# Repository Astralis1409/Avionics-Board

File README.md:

# 🛰️ CubeSat Avionics / OBC / C&DH Board

A high-reliability, low-power **On-Board Computer (OBC)** and **Command & Data Handling (C&DH)** system for VikramSat, designed for modularity, simplicity, and mission-critical operations.

> 🚀 Built for student, research, and commercial CubeSat missions.

---

## 📦 Overview

This repository contains hardware and software for the CubeSat **Avionics/OBC/C&DH subsystem**, including:

- ⚙️ Real-time telemetry and telecommand handling
- 🧠 Robust on-board computing (fault-tolerant firmware)
- 📡 Interfaces for RF, EPS, ADCS, and payload communication
- 🔒 Watchdog and fault detection mechanisms

Designed with space heritage and mission resilience in mind.

---

## 🧩 Subsystems & Features

### ✅ Key Features
- RPi RP2350 based OBC
- Redundant data buses: I2C, CAN, UART, SPI, USB
- FRAM or MRAM for persistent data storageP
- Telemetry packet generation & error checking (CRC/Checksums)
- Built-in watchdog and brownout recovery
- RTOS support (FreeRTOS)

### 📡 Interfaces
- EPS (power control, reset logic)
- [VikramSat RF subsystem](https://github.com/keyaan-07/vikramsat-rf-subsystem) (telecommand & telemetry)
- ADCS (attitude determination feedback/control)
- Payload connector (Camera)

---

## 🧠 Architecture

---

## 🛠️ Hardware

- PCB: 2 layer (FR-4)
- Components:
  - MCU: [RPi RP2350](https://raspberrypi.com/products/rp2350)
  - Memory: FRAM/MRAM (TBD)
  - Power: LDOs, and TVS/ESD protection
- Connectors: USB / Bus header / Debugger

📁 See `/hardware/` for schematics and layout (EasyEDA).

> **NOTE** : The project is under development. Hence all the components and the design may change as per the requirement.

---

## 🧪 Software

- Written in MicroPython
- RTOS support (FreeRTOS)
- Fault-tolerant state machine
- Packet parsing, command dispatcher, watchdog

📁 See `/firmware/` for source code and build instructions.

> **NOTE** : The project is under development and the software is still in its initial stages. The code may change as per the requirement.

---

## 🤝 Contributing

We welcome contributors — whether you're improving the firmware, suggesting hardware improvements, or testing!

```
# Fork, clone, and create your branch
git checkout -b feature/your-feature
```

---
## 📜 License

MIT — open-source, with mission-critical use in mind.

---

## 🧑‍🚀 Credits

Developed by Jaydev parmar

Thanks to [Hack Club](https://github.com/hackclub)

With contributions from open-source spaceflight communities 🛸

> *"Space is not the final frontier — it's just the beginning."*

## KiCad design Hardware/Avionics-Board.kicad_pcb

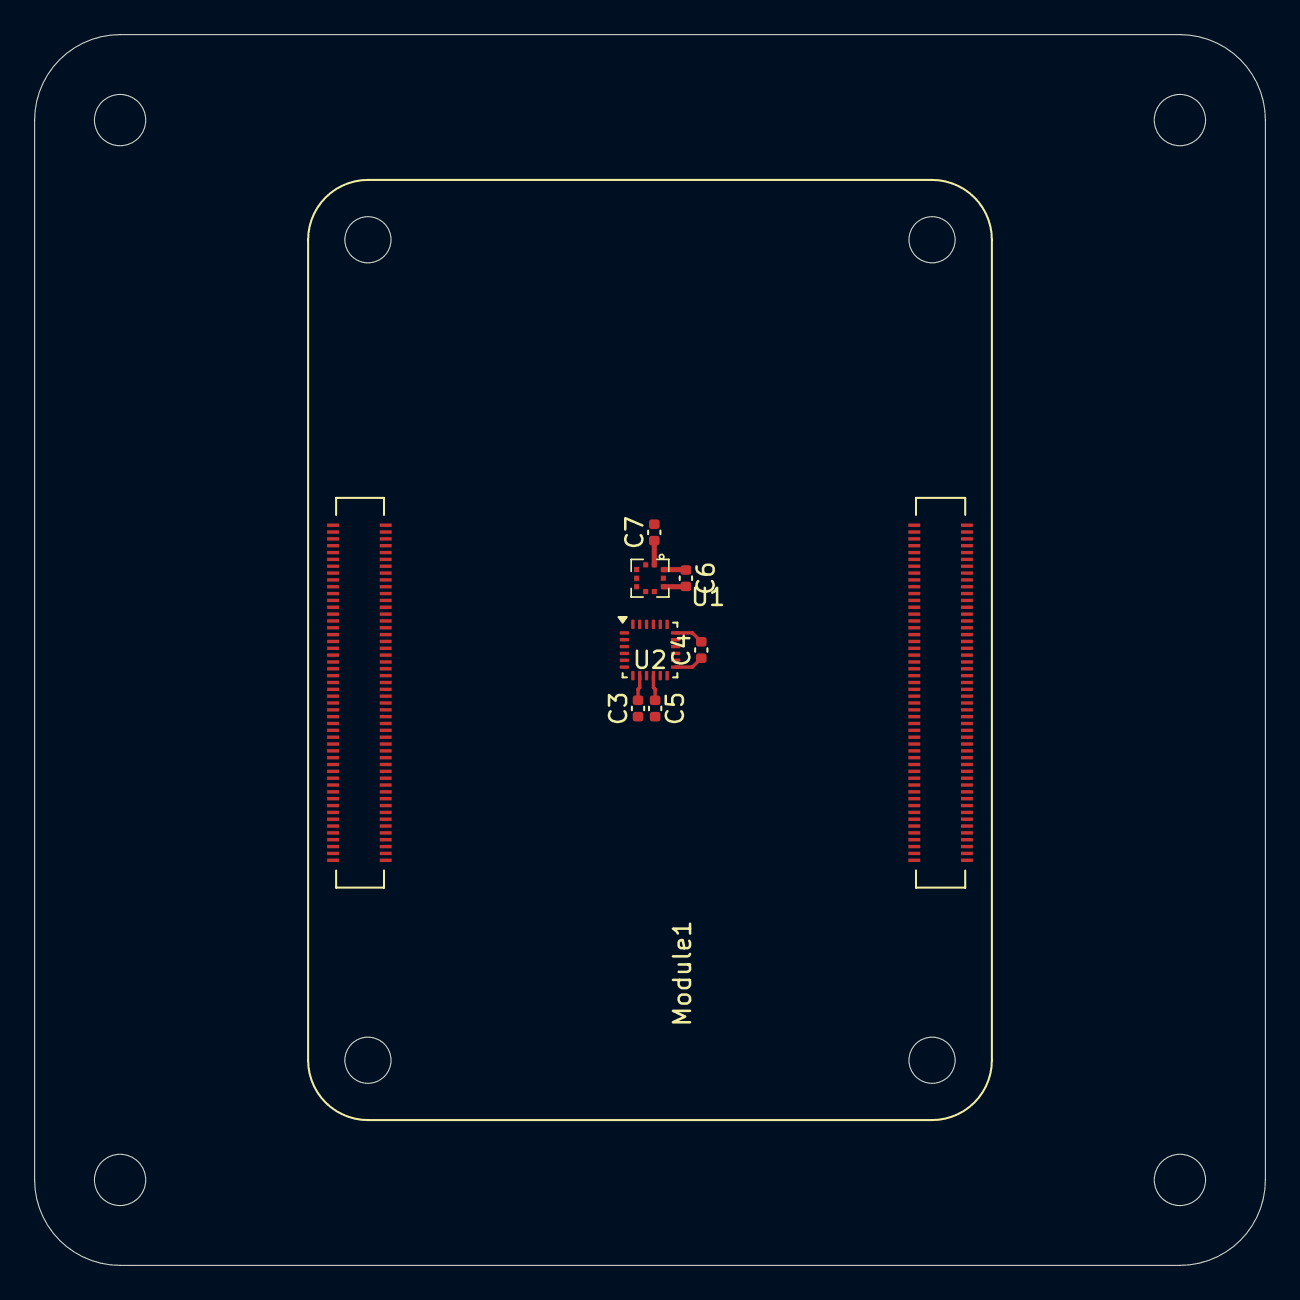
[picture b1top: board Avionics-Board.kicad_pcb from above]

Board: 2 copper layers, 72.0 x 72.0 mm, 8 parts (0 on the bottom side), 8 nets.

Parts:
C3, C4, C5, C6, C7: 100nF; C_0402_1005Metric
Module1: ComputeModule5-CM5; RPi-CM5
U1: ICM-20948; InvenSense_QFN-24_3x3mm_P0.4mm
U2: BMP-390; LGA-10_L2.0-W2.0-P0.50-BL

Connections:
+1V8: C3.2, Module1.88 (+1.8v_(Output)), Module1.90 (+1.8v_(Output)), U1.8 (VDDIO)
+3V3: C4.1, C6.1, C7.1, Module1.84 (+3.3v_(Output)), Module1.86 (+3.3v_(Output)), U1.13 (VDD), U2.1 (VDDIO), U2.10 (VDD)
+5V: Module1.77 (+5v_(Input)), Module1.79 (+5v_(Input)), Module1.81 (+5v_(Input)), Module1.83 (+5v_(Input)), Module1.85 (+5v_(Input)), Module1.87 (+5v_(Input))
/MISO1: Module1.26 (GPIO19), U1.9 (SDO/AD0), U2.5 (SDO)
/MOSI1: Module1.27 (GPIO20), U1.24 (SDA/SDI), U2.4 (SDI)
/SCLK1: Module1.25 (GPIO21), U1.23 (SCL/SCLK), U2.2 (SCK)
GND: C3.1, C4.2, C5.2, C6.2, C7.2, Module1.1 (GND), Module1.2 (GND), Module1.7 (GND), Module1.8 (GND), Module1.13 (GND), Module1.14 (GND), Module1.22 (GND), Module1.23 (GND), Module1.32 (GND), Module1.33 (GND), Module1.42 (GND), Module1.43 (GND), Module1.52 (GND), Module1.53 (GND), Module1.59 (GND), Module1.60 (GND), Module1.65 (GND), Module1.66 (GND), Module1.71 (GND), Module1.74 (GND), Module1.98 (GND), Module1.107 (GND), Module1.108 (GND), Module1.113 (GND), Module1.114 (GND), Module1.119 (GND), Module1.120 (GND), Module1.125 (GND), Module1.126 (GND), Module1.131 (GND), Module1.132 (GND), Module1.137 (GND), Module1.138 (GND), Module1.144 (GND), Module1.149 (HDMI1_CEC), Module1.150 (GND), Module1.155 (GND), Module1.156 (GND), Module1.161 (GND), Module1.162 (GND), Module1.167 (GND), Module1.168 (GND), Module1.173 (GND), Module1.174 (GND), Module1.179 (GND), Module1.180 (GND), Module1.185 (GND), Module1.186 (GND), Module1.191 (GND), Module1.192 (GND), Module1.197 (GND), Module1.198 (GND), U1.11 (FSYNC), U1.18 (GND), U1.20 (GND), U2.3 (VSS), U2.8 (VSS), U2.9 (VSS)
unnamed: C5.1, U1.10 (REGOUT)

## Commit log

2025-07-17 Add readme and journal
2025-07-18 Day-2
2025-07-20 Day-3
2025-07-20 Day-3 (Schematic and PCB)
2025-07-21 Add journal details and pics
2025-07-21 Create LICENSE
2025-07-23 Update LICENSE
2025-07-28 Day-5
2025-08-03 Day-1
2025-08-03 Day-01 fix
2025-08-03 Day-1 fix
